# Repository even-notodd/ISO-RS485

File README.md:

# ISO-RS485
## USB to RS485 and UART converter with isolation.
This is one of tools for "everyday use" once you are in embedded.
Regardless variety of cheap USB-RS485 and USB-UART "whistles" on the market and on the web, they rarely meet our expectations. There are very cheap and quite limited converters and on the other side of spectrum there are good converters usually not affordable for individuals.
Surprisingly, after many years in electronics, I still don't have a completely satisfying USB-UART and USB-RS485 tools.
So this repo contains an iterative attempt to design a tool for my own use basing on my user experience.

This version is tested and works ok.

## The main features:
- **USB-C connector.** Yes, whistles don't need USB cables but they are always near your USB port instead of being near your target hardware. So you always need long Rx/Tx/Gnd or A/B wires or some USB HUB on the desk. While it seems more natural to use generic USB-C cable which you can find everywhere currently (e.g. phone charger) and use some jumper cables etc. on serial side.
- **3 Mbaud UART** Stable UART communication on up to 3 Megabit per second with selectable voltage levels.
- **UART & RS485: both in one.** Yes, there are separate converters but I use both UART and RS485 quite frequently - so why not have them together in one device?
- **Isolation** "Safety first". Nobody likes burned hardware. UART lines are isolated with ADuM "digital isolator". Power lines are isolated with Traco isolated DC/DC. RS485 is connected via isolated transceiver So the USB side and serial side are fully isolated.
- **Switchable levels.** 3.3/5V is typical levels choice for USB-UART converters. Nevertheless, sometimes we work with projects where 1.8V UART levels are necessary and I faced lack of that feature. Thus the levels here can be chosen among 1.8, 3.3 and 5V (with a jumper).
- **RS485 autodirection.** In current version is handled by FT230.
- **Indication:** 3 LEDs for Rx Tx and isolated power

## Versions history
** Initially ** there were 2 similar designs in parallel: based on FT230 and CH340G.I used CH340 in several devices before and didn't face any issues with them (at least on low baud rates). Nevertheless, its availability is questionable and receiving parts from LCSC is often problematic, while I wanted the device to be reproduceable with one-stop order from big suppliers like Mouser or Digikey. Also I don't like CH340 drivers distribution as well as documentation. Its price makes it really attractive for DIY or projects where cost optimization is important but my personal feeling is the chip is immature for commercial projects or open source. So CH340 version was excluded from further development and is extinct by now.
Optical isolation was applied for data lines in that first version. And it was a wrong decision. I assembled one piece to have a look, the optocouplers expectedly limited the speed and I found the shape of signal completely dissatisfying. There was an option to use better optocouplers and correct the circuit but by that time I wanted to add 1.8V levels and to make signal looking better. So I decided to get rid of optical isolation shifting to isolated level shifter for UART.
** Current version** is being built around FT230, isolated RS485 transceiver, ADuM121 digital isolator for UART and multi-voltage isolated power supply for level shifting.

## Driver
FTDI FT230 driver is available on [manufacturer's website](https://ftdichip.com/drivers/).

## Assembly & Configuration
When using a new FT230 chip, default assignment of CBUS0...CBUS must be reconfigured first in MTP memory (as there is some mismatch between datasheet and actual values). For that purpose use [FT_PROG software from FTDI](https://ftdichip.com/utilities/): 
Devices -> Scan and Parse -> CBUS signals. Then assign CBUS according to schematics and program.

LDO is a bit hard to assembly without stencil, (any extra solder paste on EP pulls IC up breaking other connections), be attentive!

## Testing and Limitations
The device in the latest version was tested in UART mode (serial communication between 2 pieces) on all designed voltage levels (5V, 3.3V and 1.8V) with signals shape observation on baud rates up to 3 Mbps and results looked appropriate. 3 Mbps speed corresponds to limit declared by FTDI datasheet. 
In RS485 mode, the stability of transmission and signal "health" in our observation stayed appropriate up to 500 kbps, so there is some room for further improvement.

## ToDo
- replace AP7345D or modify footprint to prevent assembly issues;
- improve RS485 signal to increase its speed up to FT230 limit.

## License
This project is licensed under:
- **Hardware (KiCad design files)**: Licensed under **CERN-OHL-W-2.0**, which allows modification and commercial use with attribution.

See the  for details.

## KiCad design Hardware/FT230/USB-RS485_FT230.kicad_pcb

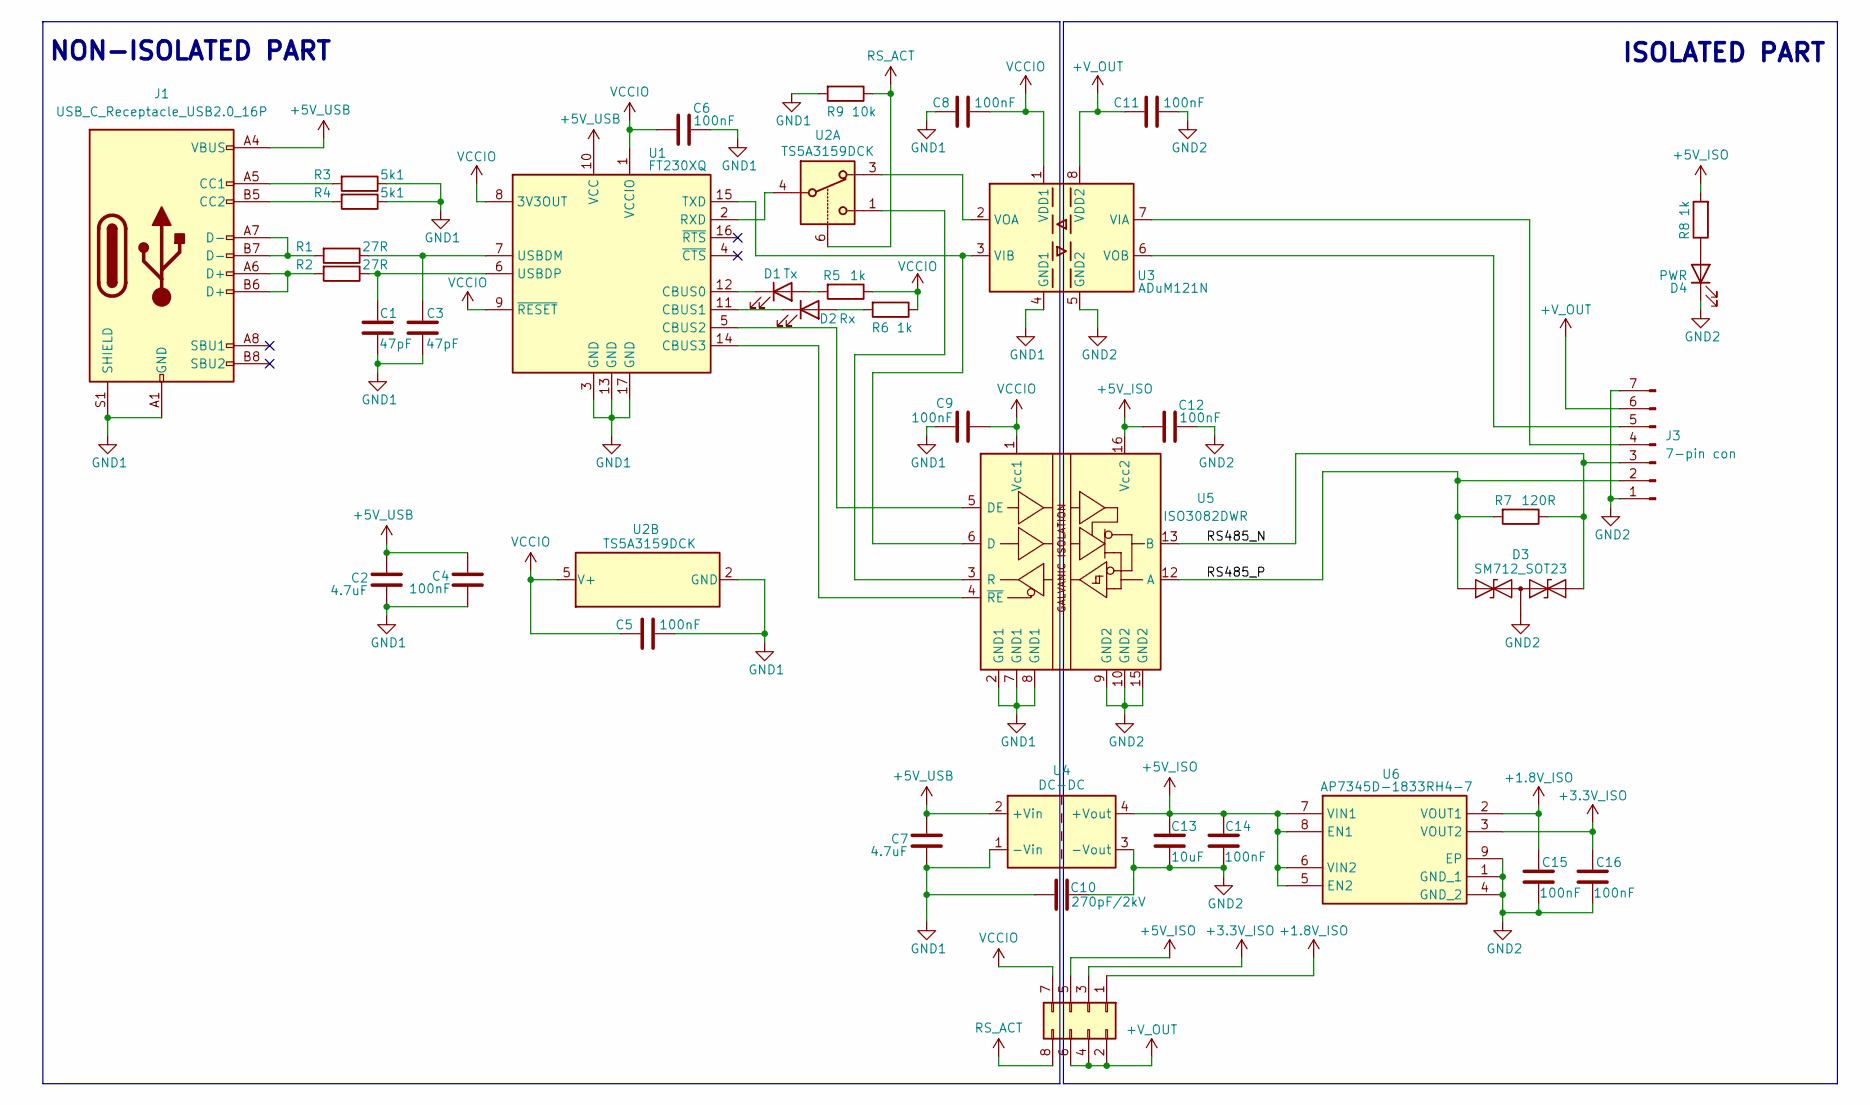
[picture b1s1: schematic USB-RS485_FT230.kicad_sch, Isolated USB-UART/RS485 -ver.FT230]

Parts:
C1, C3: 47pF; C_0805_2012Metric; MPN 885012007032
C2, C7: 4.7uF; C_0805_2012Metric; MPN 885012207053
C4, C5, C6, C8, C9, C11, C12, C14, C15, C16: 100nF; C_0805_2012Metric; MPN 885012207098
C10: 270pF/2kV; C_1206_3216Metric; MPN C1206C271MGRACTU
C13: 10uF; C_0805_2012Metric; MPN 885012107004
D1: Tx; LED_0805_2012Metric; MPN 150080YS75000
D2: Rx; LED_0805_2012Metric; MPN 150224GS73100
D3: SM712_SOT23; SOT-23; MPN SM712-02HTG
D4: PWR; LED_0805_2012Metric; MPN 150080RS75000
J1: USB_C_Receptacle_USB2.0_16P; USB_C_Receptacle_GCT_USB4110; MPN USB4110-GF-A
J2: Conn_02x04_Odd_Even; PinHeader_2x04_P2.54mm_Vertical
J3: 7-pin con; PinHeader_1x07_P2.54mm_Vertical; MPN 10129379-907001BLF
R1, R2: 27R; R_0805_2012Metric; MPN CR0805-FX-27R0ELF
R3, R4: 5k1; R_0805_2012Metric; MPN 560112120019
R5, R6, R8: 1k; R_0805_2012Metric; MPN CR0805-FX-1001ELF
R7: 120R; R_0805_2012Metric; MPN CHP0805AFX-1200ELF
R9: 10k; R_0805_2012Metric
U1: FT230XQ; QFN-16-1EP_4x4mm_P0.65mm_EP2.1x2.1mm; MPN FT230XQ-R
U2: TS5A3159DCK; SOT-363_SC-70-6; MPN TS5A3159DCK
U3: ADuM121N; SOIC-8_3.9x4.9mm_P1.27mm; MPN ADUM121N0BRZ-RL7
U4: DC-DC; Converter_DCDC_TRACO_TEA1-xxxx_THT; MPN TEA 1-0505
U5: ISO3082DWR; SOIC-16W_7.5x10.3mm_P1.27mm; MPN ISO3082DWR
U6: AP7345D-1833RH4-7; AP7345D1833RH47; Mouser Part Number 621-AP7345D1833RH4-7

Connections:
+1.8V_ISO: C15.2, J2.1, U6.2 (VOUT1)
+3.3V_ISO: C16.2, J2.3, U6.3 (VOUT2)
+5V_ISO: C12.1, C13.2, C14.2, J2.5, R8.2, U4.4 (+Vout), U5.16 (Vcc2), U6.5 (EN2), U6.6 (VIN2), U6.7 (VIN1), U6.8 (EN1)
+5V_USB: C2.2, C4.1, C7.2, J1.A4 (VBUS), J1.A9 (VBUS), J1.B4 (VBUS), J1.B9 (VBUS), U1.10 (VCC), U4.2 (+Vin)
+V_OUT: C11.1, J2.2, J2.4, J2.6, J3.6, U3.8 (VDD2)
/RS485_N: D3.2 (A2), J3.3, R7.1, U5.13 (B)
/RS485_P: D3.1 (A1), J3.2, R7.2, U5.12 (A)
GND1: C1.2, C2.1, C3.2, C4.2, C5.2, C6.2, C7.1, C8.1, C9.1, C10.1, J1.A1 (GND), J1.A12 (GND), J1.B1 (GND), J1.B12 (GND), J1.S1 (SHIELD), R3.1, R4.1, R9.2, U1.3 (GND), U1.13 (GND), U1.17 (GND), U2.2 (GND), U3.4 (GND1), U4.1 (-Vin), U5.2 (GND1), U5.7 (GND1), U5.8 (GND1)
GND2: C10.2, C11.2, C12.2, C13.1, C14.1, C15.1, C16.1, D3.3 (common), D4.1 (K), J3.1, J3.7, U3.5 (GND2), U4.3 (-Vout), U5.9 (GND2), U5.10 (GND2), U5.15 (GND2), U6.1 (GND_1), U6.4 (GND_2), U6.9 (EP)
unnamed: D1.2 (A), R5.2
unnamed: D1.1 (K), U1.12 (CBUS0)
unnamed: D2.2 (A), R6.2
unnamed: D2.1 (K), U1.11 (CBUS1)
unnamed: D4.2 (A), R8.1
unnamed: J1.A5 (CC1), R3.2
unnamed: J1.B5 (CC2), R4.2
unnamed: J1.A6 (D+), J1.B6 (D+), R2.2
unnamed: J1.A7 (D-), J1.B7 (D-), R1.2
unnamed: J3.4, U3.7 (VIA)
unnamed: J3.5, U3.6 (VOB)
unnamed: U1.5 (CBUS2), U5.5 (DE)
unnamed: U1.14 (CBUS3), U5.4 (~RE)
unnamed: U1.2 (RXD), U2.4
unnamed: U1.15 (TXD), U3.3 (VIB), U5.6 (D)
unnamed: C3.1, R1.1, U1.7 (USBDM)
unnamed: C1.1, R2.1, U1.6 (USBDP)
unnamed: U2.3, U3.2 (VOA)
unnamed: U2.1, U5.3 (R)
RS_ACT: J2.8, R9.1, U2.6
VCCIO: C5.1, C6.1, C8.2, C9.2, J2.7, R5.1, R6.1, U1.1 (VCCIO), U1.8 (3V3OUT), U1.9 (~RESET), U2.5 (V+), U3.1 (VDD1), U5.1 (Vcc1)

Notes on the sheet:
NON-ISOLATED PART
ISOLATED PART

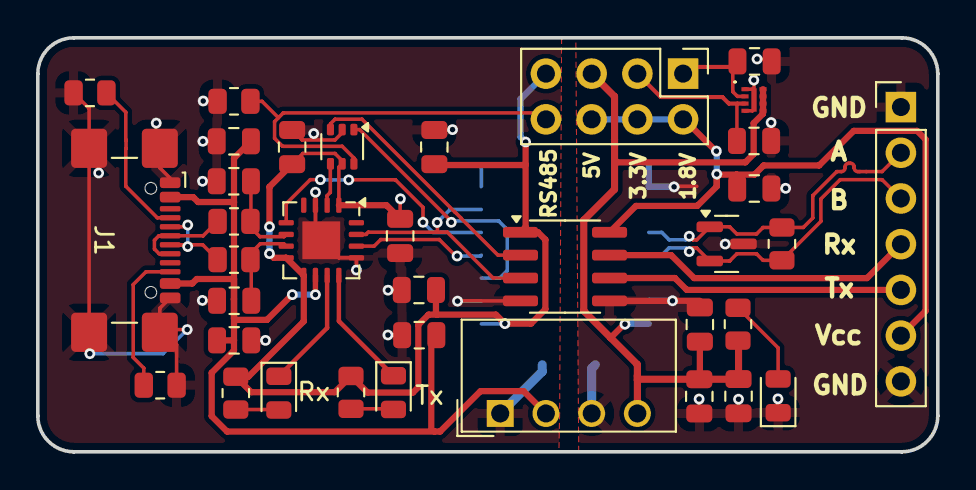
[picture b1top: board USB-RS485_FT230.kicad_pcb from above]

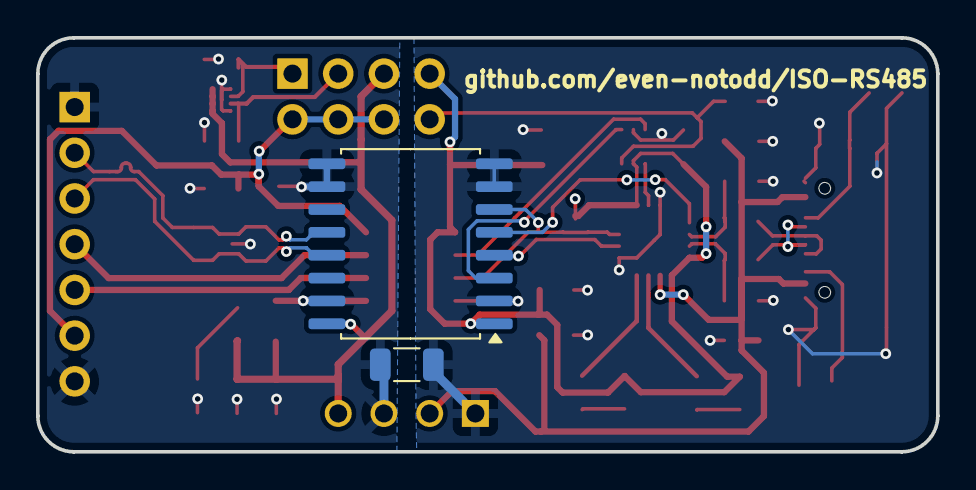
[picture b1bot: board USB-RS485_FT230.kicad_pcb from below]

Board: 2 copper layers, 50.0 x 23.0 mm, 38 parts (2 on the bottom side), 30 nets.

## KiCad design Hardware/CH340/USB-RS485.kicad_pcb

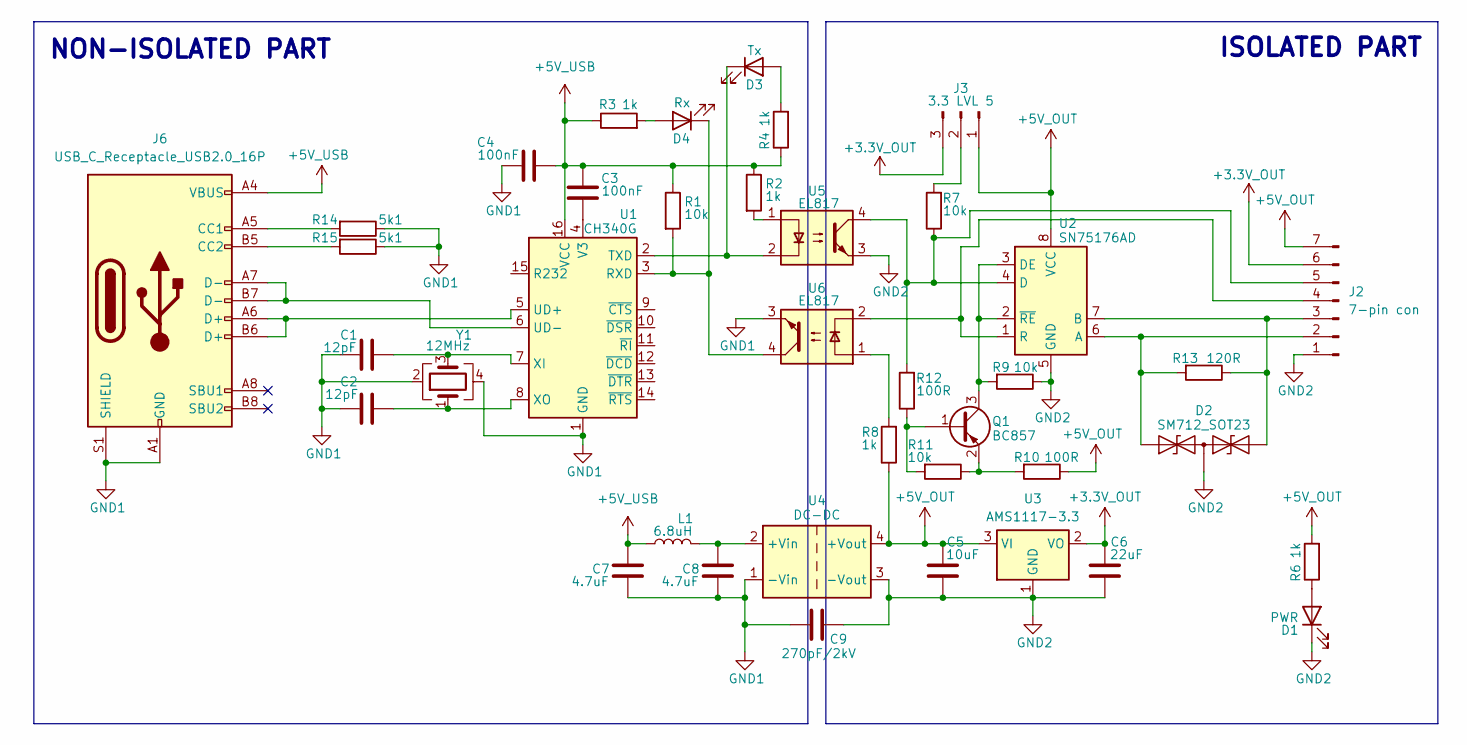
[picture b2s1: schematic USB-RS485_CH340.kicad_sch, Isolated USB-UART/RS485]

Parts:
C1, C2: 12pF; C_0805_2012Metric; LCSC PN C106201
C3, C4: 100nF; C_0805_2012Metric; LCSC PN C14663
C5: 10uF; C_0805_2012Metric; LCSC PN C315248
C6: 22uF; C_0805_2012Metric; LCSC PN C415703
C7, C8: 4.7uF; C_0805_2012Metric; LCSC PN C2858031
C9: 270pF/2kV; C_1206_3216Metric; LCSC PN C7393992
D1: PWR; LED_0805_2012Metric
D2: SM712_SOT23; SOT-23
D3: Tx; LED_0805_2012Metric
D4: Rx; LED_0805_2012Metric
J2: 7-pin con; PinHeader_1x07_P2.54mm_Vertical
J3: 3.3 LVL 5; PinHeader_1x03_P2.54mm_Vertical
J6: USB_C_Receptacle_USB2.0_16P; USB_C_Receptacle_GCT_USB4110; MPN USB4110-GF-A
L1: 6.8uH; L_1206_3216Metric; LCSC PN C395031
Q1: BC857; SOT-23
R1, R7, R9, R11: 10k; R_0805_2012Metric
R2, R3, R4, R6, R8: 1k; R_0805_2012Metric
R10, R12: 100R; R_0805_2012Metric
R13: 120R; R_0805_2012Metric
R14, R15: 5k1; R_0805_2012Metric; MPN 560112120019
U1: CH340G; SOIC-16_3.9x9.9mm_P1.27mm; LCSC PN C14267
U2: SN75176AD; SOIC-8_3.9x4.9mm_P1.27mm; LCSC PN C7063
U3: AMS1117-3.3; SOT-223-3_TabPin2; LCSC PN C110474
U4: DC-DC; Converter_DCDC_TRACO_TEA1-xxxx_THT; LCSC PN C7465178
U5, U6: EL817; SMDIP-4_W9.53mm; LCSC PN C3031553
Y1: 12MHz; Crystal_SMD_3225-4Pin_3.2x2.5mm; LCSC PN C133337

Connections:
+3.3V_OUT: C6.2, J2.6, J3.3, U3.2 (VO)
+5V_OUT: C5.2, J2.7, J3.1, R6.2, R8.1, R10.1, U2.8 (VCC), U3.3 (VI), U4.4 (+Vout)
+5V_USB: C3.2, C4.1, C7.2, J6.A4 (VBUS), J6.A9 (VBUS), J6.B4 (VBUS), J6.B9 (VBUS), L1.1, R1.1, R2.1, R3.1, R4.1, U1.16 (VCC)
GND1: C1.1, C2.1, C4.2, C7.1, C8.1, C9.1, J6.A1 (GND), J6.A12 (GND), J6.B1 (GND), J6.B12 (GND), J6.S1 (SHIELD), R14.1, R15.1, U1.1 (GND), U4.1 (-Vin), U6.3, Y1.2, Y1.4
GND2: C5.1, C6.1, C9.2, D1.1 (K), D2.3 (common), J2.1, R9.1, U2.5 (GND), U3.1 (GND), U4.3 (-Vout), U5.3
unnamed: D1.2 (A), R6.1
unnamed: D2.1 (A1), J2.2, R13.2, U2.6 (A)
unnamed: D2.2 (A2), J2.3, R13.1, U2.7 (B)
unnamed: D3.2 (A), R4.2
unnamed: D3.1 (K), U1.2 (TXD), U5.2
unnamed: D4.2 (A), R3.2
unnamed: D4.1 (K), R1.2, U1.3 (RXD), U6.4
unnamed: J2.4, U2.1 (R), U6.2
unnamed: J2.5, R7.1, R12.2, U2.4 (D), U5.4
unnamed: J3.2, R7.2
unnamed: J6.A5 (CC1), R14.2
unnamed: J6.B5 (CC2), R15.2
unnamed: Q1.1 (B), R11.2, R12.1
unnamed: Q1.3 (C), R9.2, U2.2 (~RE), U2.3 (DE)
unnamed: Q1.2 (E), R10.2, R11.1
unnamed: R2.2, U5.1
unnamed: R8.2, U6.1
unnamed: J6.A6 (D+), J6.B6 (D+), U1.5 (UD+)
unnamed: J6.A7 (D-), J6.B7 (D-), U1.6 (UD-)
unnamed: C3.1, U1.4 (V3)
unnamed: C1.2, U1.7 (XI), Y1.3
unnamed: C2.2, U1.8 (XO), Y1.1
unnamed: C8.2, L1.2, U4.2 (+Vin)

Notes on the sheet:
NON-ISOLATED PART
ISOLATED PART

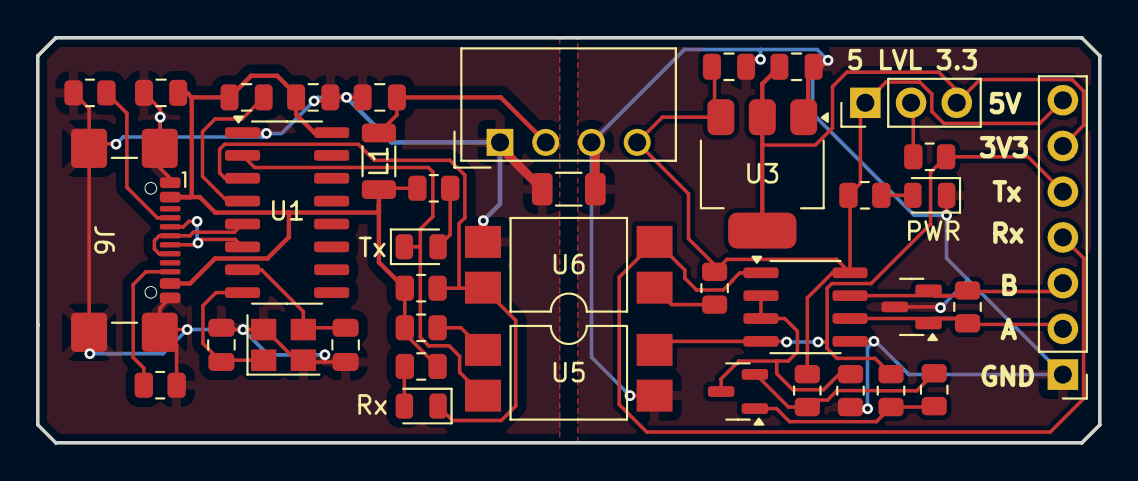
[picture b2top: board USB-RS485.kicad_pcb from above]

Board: 2 copper layers, 59.0 x 22.5 mm, 39 parts (0 on the bottom side), 28 nets.

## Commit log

2025-05-25 Kicad design
2025-05-27 FTDI added
2025-05-28 FT230 schematics
2025-05-29 FT230 PCB - in progress
2025-05-29 FT230 schematics PDF export
2025-05-29 FT230 BOM and fix
2025-06-06 FT230 gerbers export
2025-06-15 schematics cosmetic change
2025-06-24 -opto +Adum & 1.8
2025-06-29 ADuM iteration. Readme.
2025-07-05 schematics update
2025-07-24 schematics change
2025-07-27 layout update
2025-07-27 gerbers added
2025-08-09 CBUS-configs
2025-08-12 Readme & testing
2025-12-25 Readme clean-up
